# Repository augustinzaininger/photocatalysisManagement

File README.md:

# photocatalysisManagement
PCB Layouts, firmware and software for management of photocatalysis experimental system consisting of MFCs, Solenoid Valves etc

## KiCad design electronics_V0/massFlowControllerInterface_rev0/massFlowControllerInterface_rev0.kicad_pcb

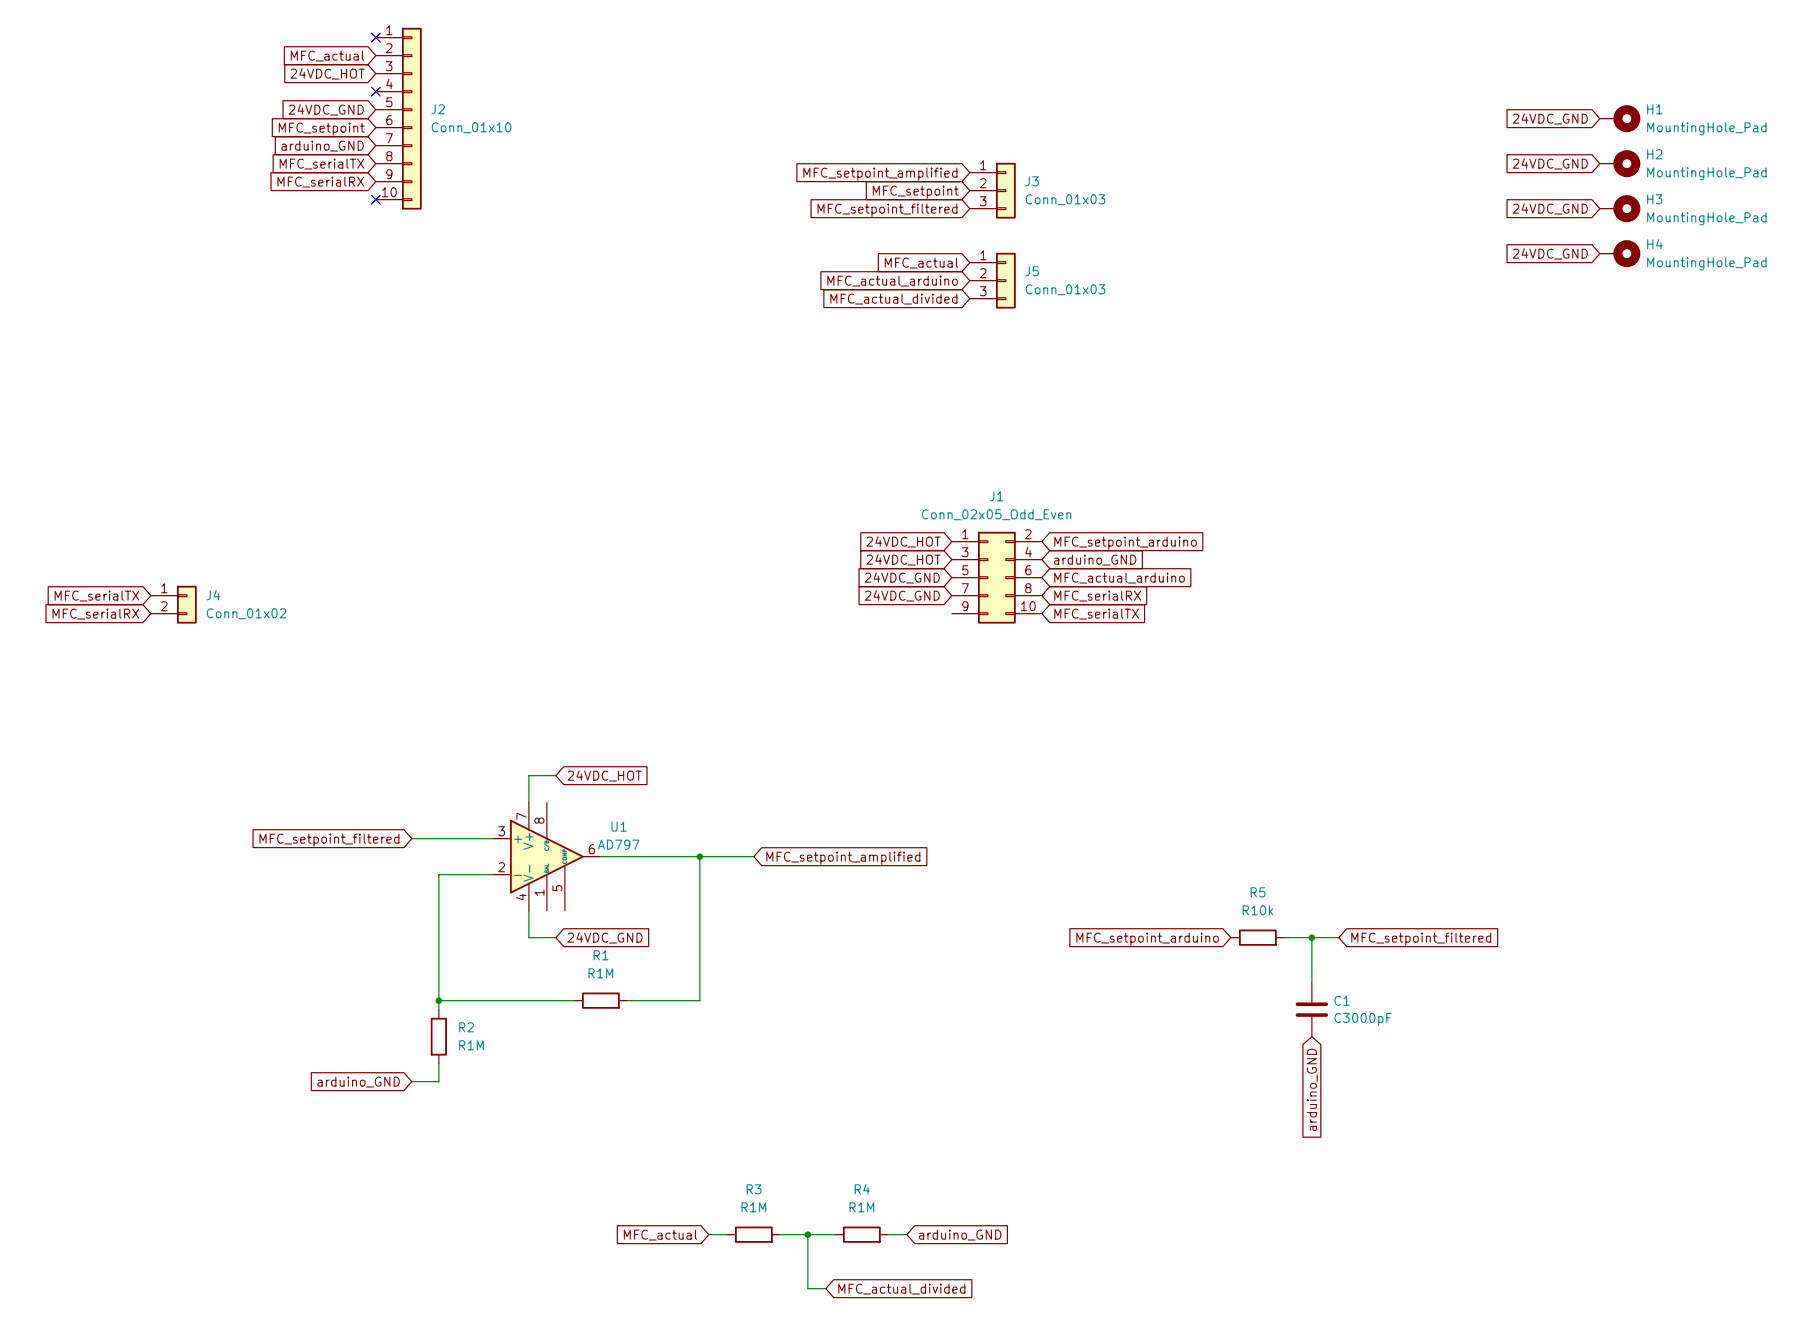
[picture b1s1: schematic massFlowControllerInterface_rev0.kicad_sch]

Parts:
C1: C3000pF; C_0805_2012Metric_Pad1.18x1.45mm_HandSolder
H1, H2, H3, H4: MountingHole_Pad; MountingHole_3.2mm_M3_Pad_Via
J1: Conn_02x05_Odd_Even; PinHeader_2x05_P2.54mm_Vertical
J2: Conn_01x10; multicomp_screwTerminal_10Way_MP008518
J3, J5: Conn_01x03; PinHeader_1x03_P2.54mm_Vertical
J4: Conn_01x02; multicomp_screwTerminal_2Way_MP008513
R1, R2, R3, R4: R1M; R_2010_5025Metric_Pad1.40x2.65mm_HandSolder
R5: R10k; R_2010_5025Metric_Pad1.40x2.65mm_HandSolder
U1: AD797; DIP-8_W7.62mm

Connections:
24VDC_GND: H1.1, H2.1, H3.1, H4.1, J1.5, J1.7, J2.5, U1.4 (V-)
24VDC_HOT: J1.1, J1.3, J2.3, U1.7 (V+)
MFC_actual: J2.2, J5.1, R3.1
MFC_actual_arduino: J1.6, J5.2
MFC_actual_divided: J5.3, R3.2, R4.1
MFC_serialRX: J1.8, J2.9, J4.2
MFC_serialTX: J1.10, J2.8, J4.1
MFC_setpoint: J2.6, J3.2
MFC_setpoint_amplified: J3.1, R1.2, U1.6
MFC_setpoint_arduino: J1.2, R5.1
MFC_setpoint_filtered: C1.1, J3.3, R5.2, U1.3 (+)
unnamed: R1.1, R2.1, U1.2 (-)
arduino_GND: C1.2, J1.4, J2.7, R2.2, R4.2

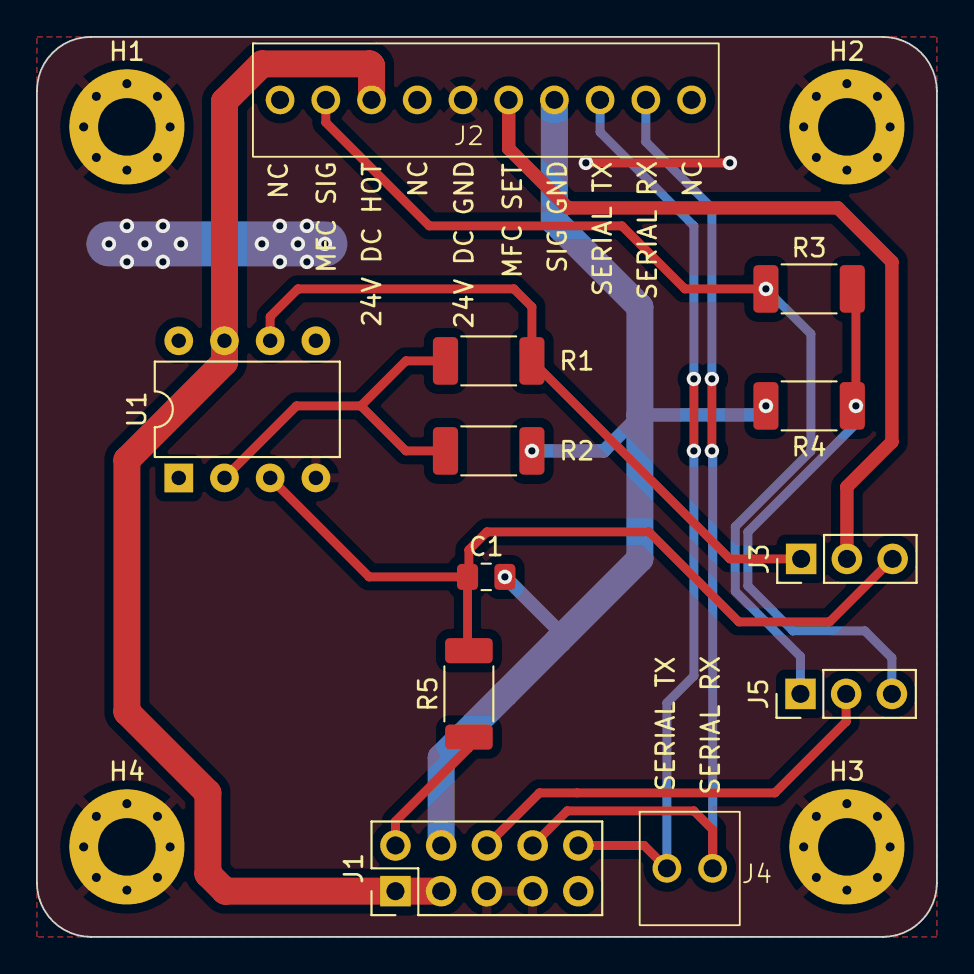
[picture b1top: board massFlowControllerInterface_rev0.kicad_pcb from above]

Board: 2 copper layers, 50.0 x 50.0 mm, 16 parts (0 on the bottom side), 13 nets.

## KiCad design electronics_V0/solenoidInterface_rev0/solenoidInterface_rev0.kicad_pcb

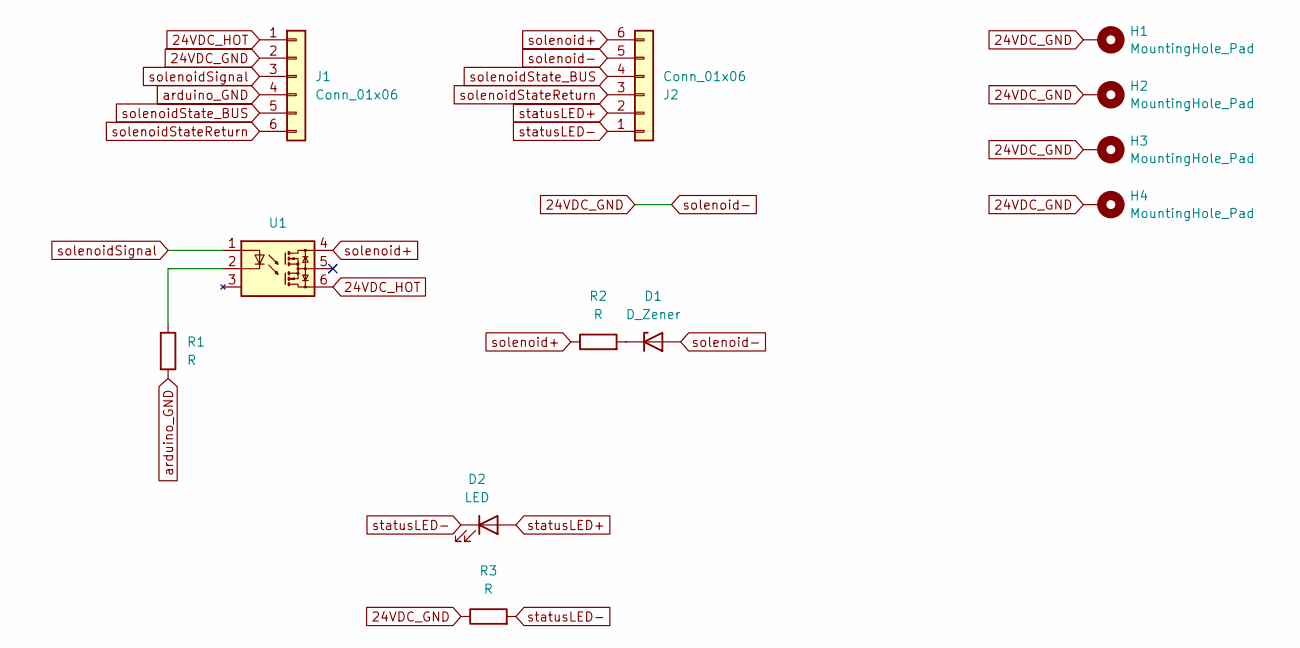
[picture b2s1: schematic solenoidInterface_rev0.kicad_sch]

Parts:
D1: D_Zener; D_A-405_P7.62mm_Horizontal
D2: LED; LED_D3.0mm
H1, H2, H3, H4: MountingHole_Pad; MountingHole_2.5mm_Pad_Via
J1: Conn_01x06; PinHeader_1x06_P2.54mm_Horizontal
J2: Conn_01x06; phoenixContact_MPT_05_254-6way
R1, R2, R3: R; R_2010_5025Metric_Pad1.40x2.65mm_HandSolder
U1: DIP-6_W7.62mm

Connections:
24VDC_GND: D1.2 (A), H1.1, H2.1, H3.1, H4.1, J1.2, J2.5, R3.1
24VDC_HOT: J1.1, U1.6
unnamed: D1.1 (K), R2.2
unnamed: R1.1, U1.2
arduino_GND: J1.4, R1.2
solenoid+: J2.6, R2.1, U1.4
solenoidSignal: J1.3, U1.1
solenoidStateReturn: J1.6, J2.3
solenoidState_BUS: J1.5, J2.4
statusLED+: D2.2 (A), J2.2
statusLED-: D2.1 (K), J2.1, R3.2

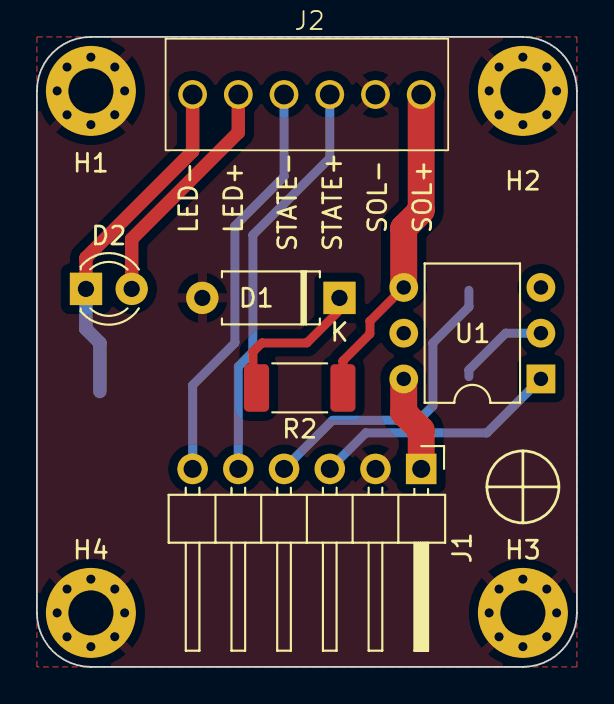
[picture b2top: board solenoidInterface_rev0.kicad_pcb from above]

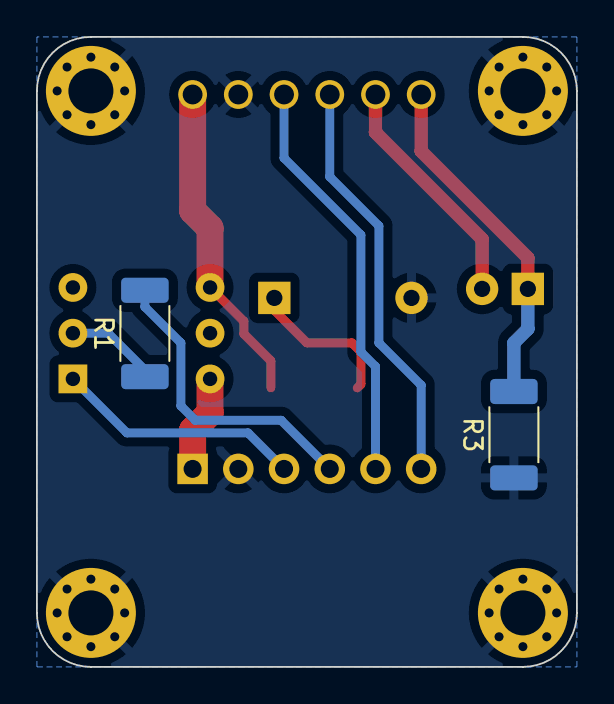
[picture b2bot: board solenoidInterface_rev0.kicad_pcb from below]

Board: 2 copper layers, 30.0 x 35.0 mm, 12 parts (2 on the bottom side), 11 nets.

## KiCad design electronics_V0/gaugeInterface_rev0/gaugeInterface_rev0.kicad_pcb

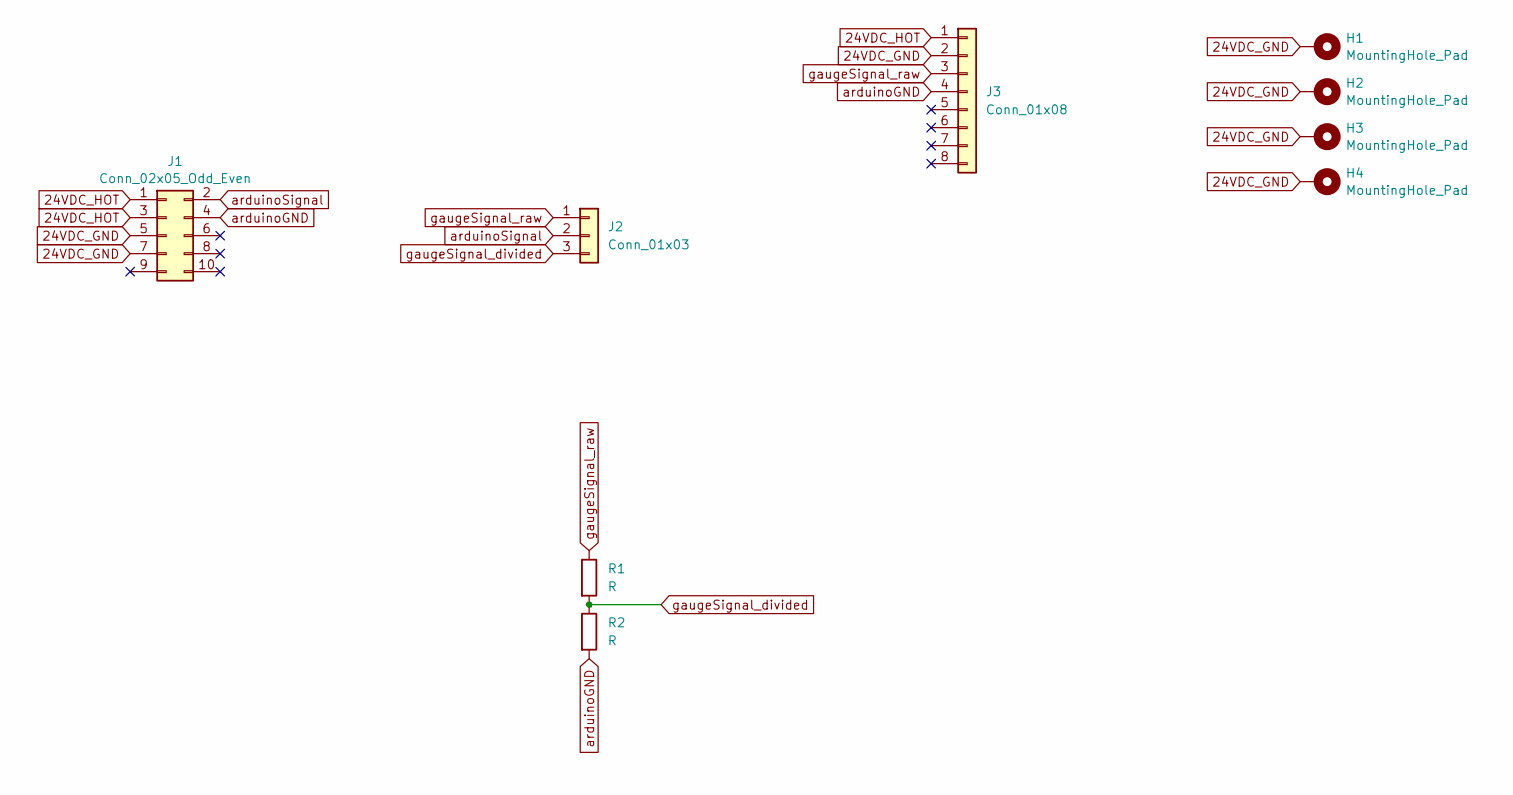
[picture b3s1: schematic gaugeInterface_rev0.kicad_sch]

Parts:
H1, H2, H3, H4: MountingHole_Pad; MountingHole_3.2mm_M3_Pad_Via
J1: Conn_02x05_Odd_Even; PinHeader_2x05_P2.54mm_Vertical
J2: Conn_01x03; PinHeader_1x03_P2.54mm_Vertical
J3: Conn_01x08; phoenixContact_MPT_05_254-8way
R1, R2: R; R_2010_5025Metric_Pad1.40x2.65mm_HandSolder

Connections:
24VDC_GND: H1.1, H2.1, H3.1, H4.1, J1.5, J1.7, J3.2
24VDC_HOT: J1.1, J1.3, J3.1
arduinoGND: J1.4, J3.4, R2.2
arduinoSignal: J1.2, J2.2
gaugeSignal_divided: J2.3, R1.2, R2.1
gaugeSignal_raw: J2.1, J3.3, R1.1

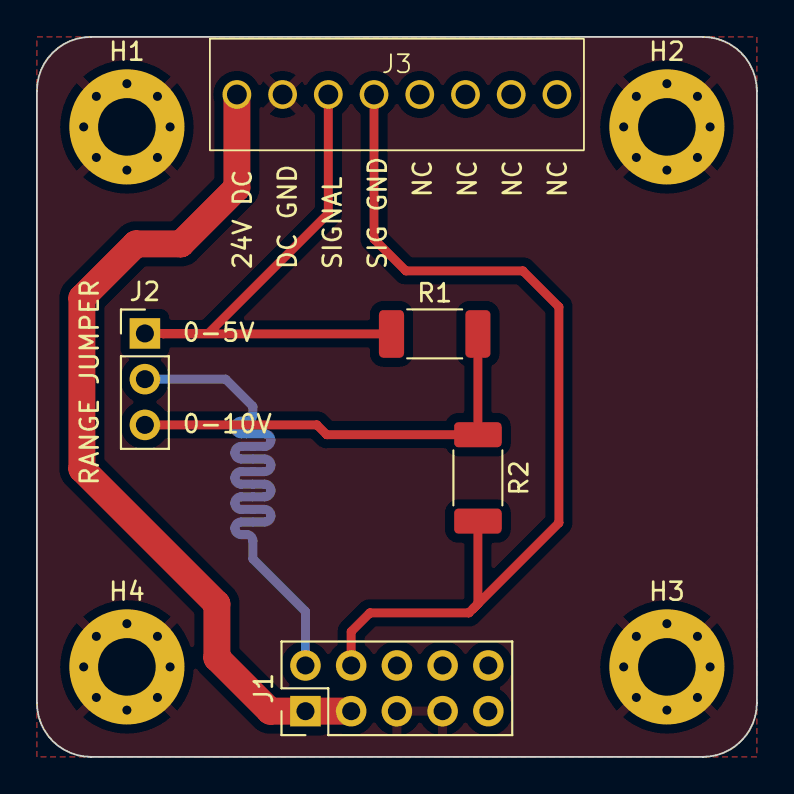
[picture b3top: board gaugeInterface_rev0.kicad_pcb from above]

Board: 2 copper layers, 40.0 x 40.0 mm, 9 parts (0 on the bottom side), 6 nets.

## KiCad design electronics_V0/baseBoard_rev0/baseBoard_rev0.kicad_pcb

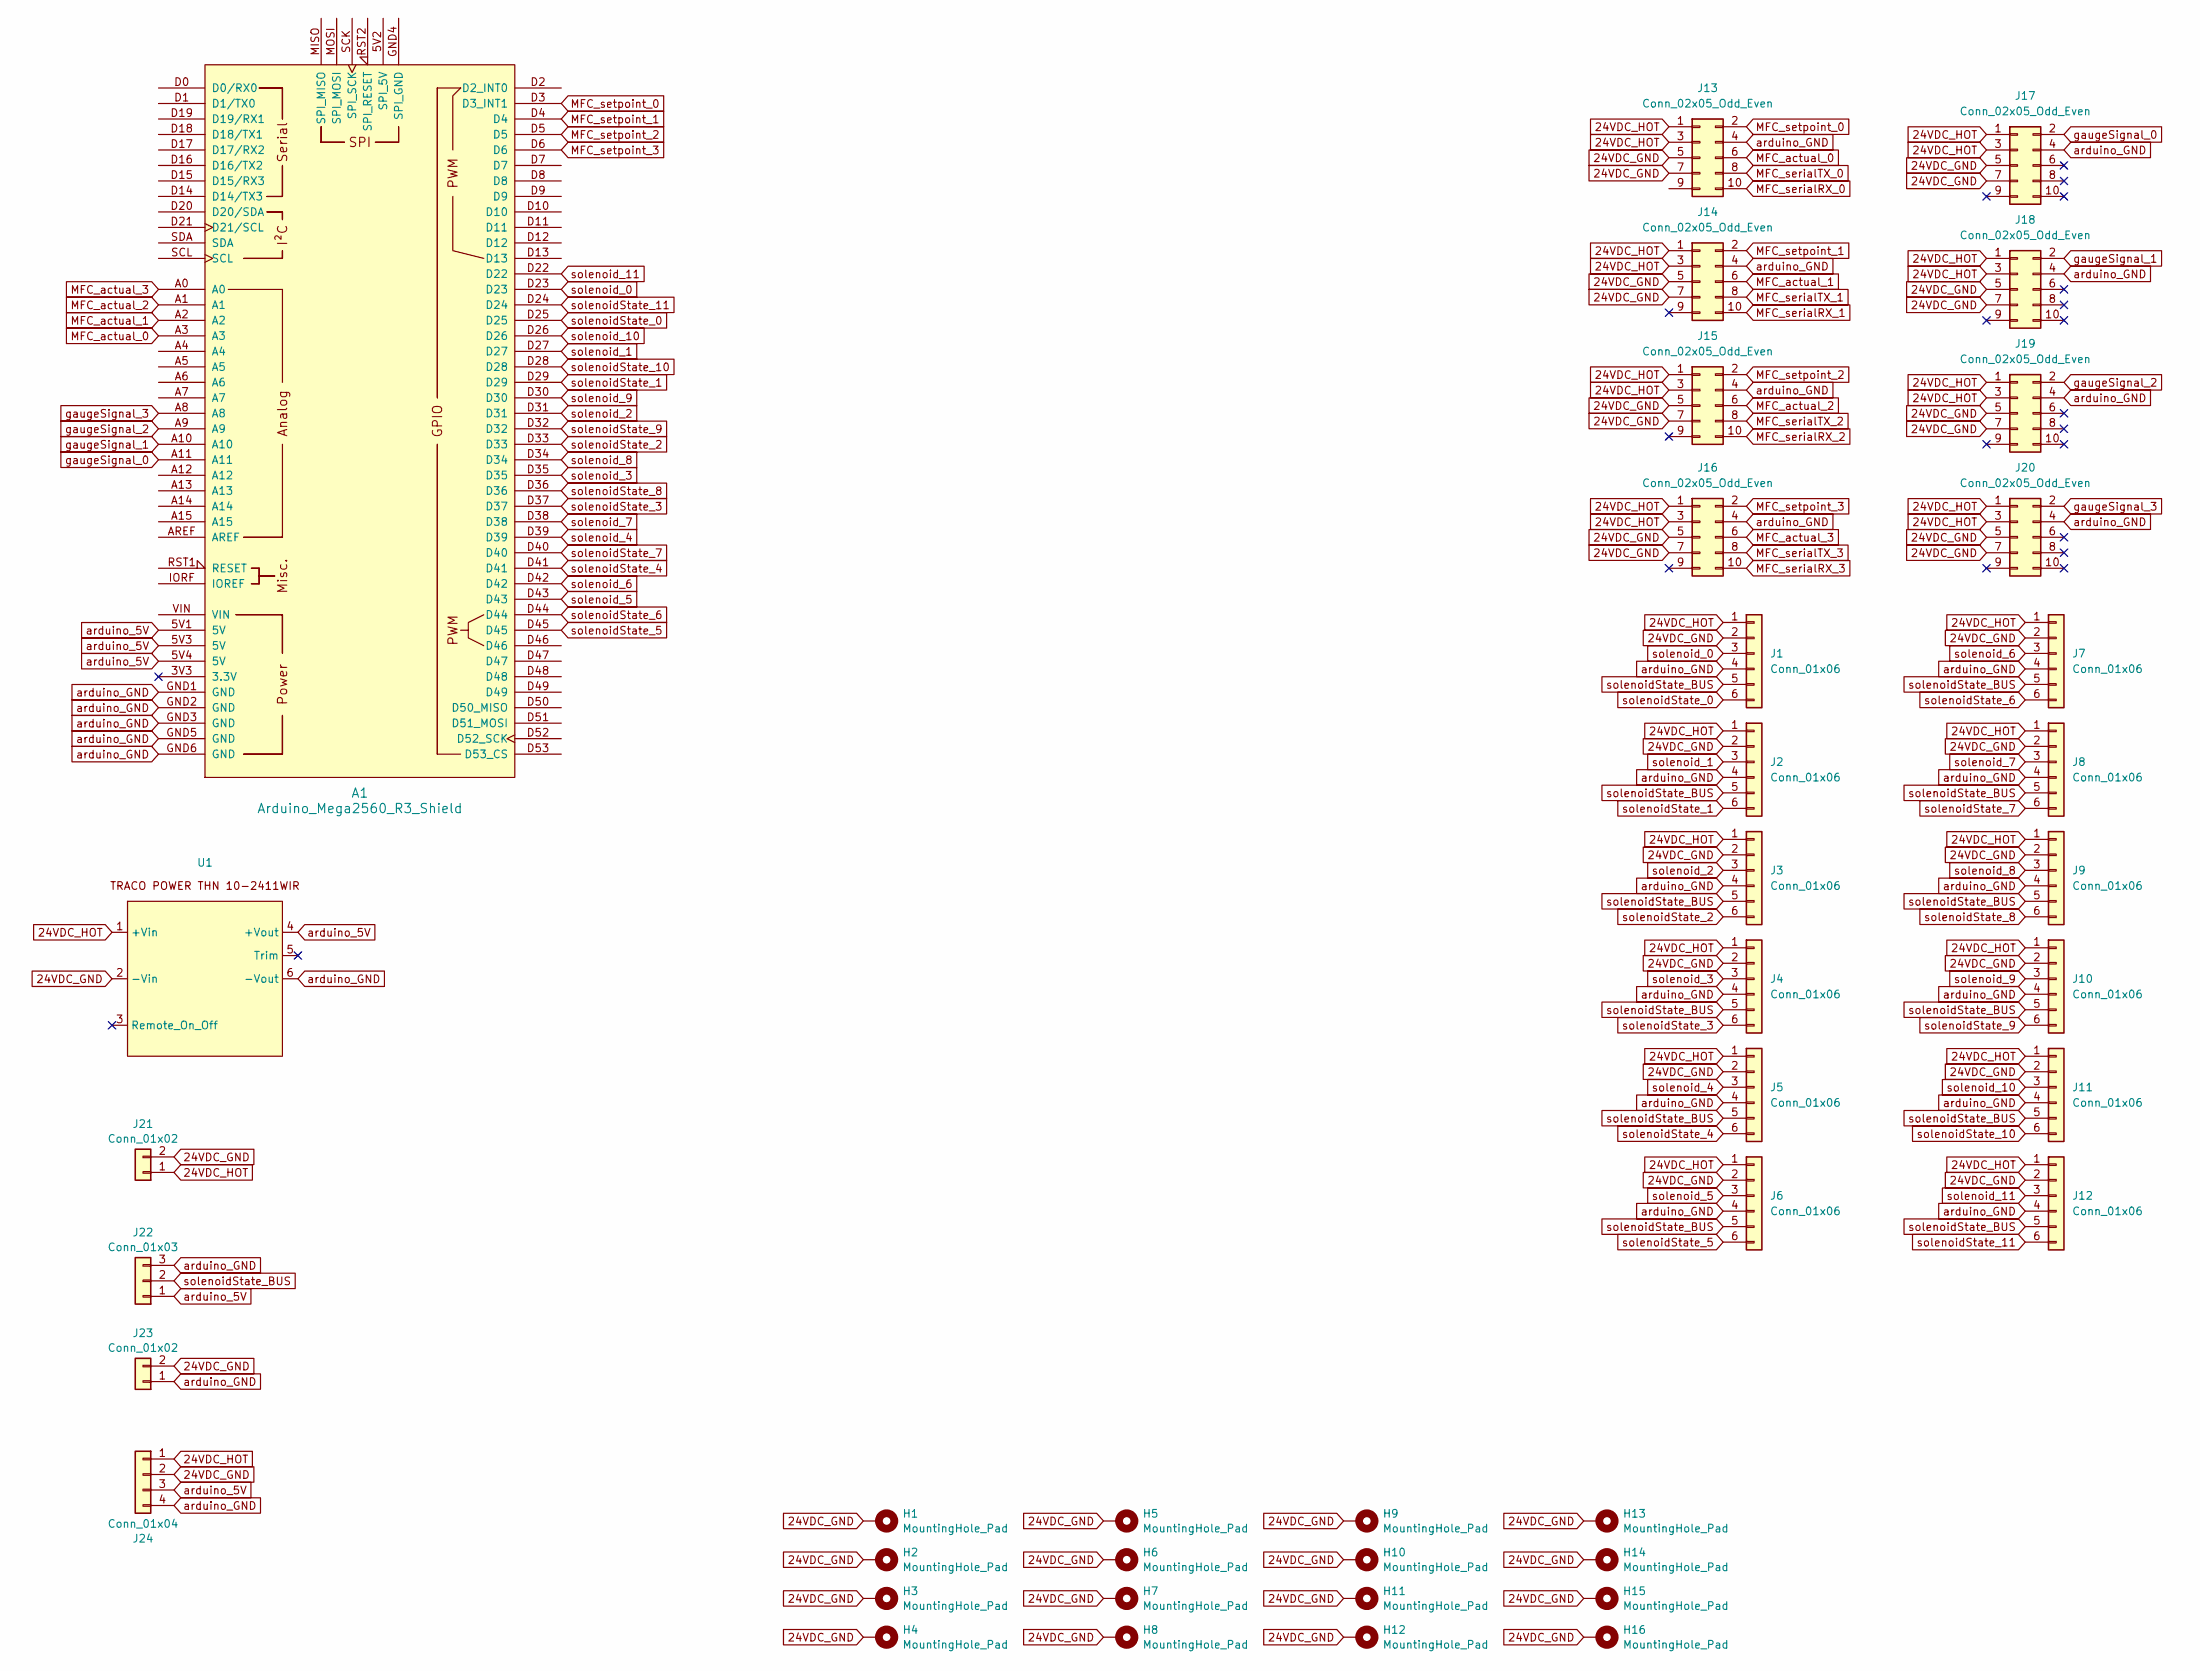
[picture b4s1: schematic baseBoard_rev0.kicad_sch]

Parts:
A1: Arduino_Mega2560_R3_Shield
H1, H2, H3, H4, H5, H6, H7, H8, H9, H10, H11, H12, H13, H14, H15, H16: MountingHole_Pad; MountingHole_3.2mm_M3_Pad_Via
J1, J2, J3, J4, J5, J6, J7, J8, J9, J10, J11, J12: Conn_01x06; PinSocket_1x06_P2.54mm_Vertical
J13, J14, J15, J16, J17, J18, J19, J20: Conn_02x05_Odd_Even; PinHeader_2x05_P2.54mm_Vertical
J21: Conn_01x02; TerminalBlock_Phoenix_MKDS-1,5-2-5.08_1x02_P5.08mm_Horizont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
J22: Conn_01x03; PinHeader_1x03_P2.54mm_Vertical
J23: Conn_01x02; PinHeader_1x02_P2.54mm_Vertical
J24: Conn_01x04; PinHeader_1x04_P2.54mm_Vertical
U1: THN102410WIR

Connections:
24VDC_GND: H1.1, H2.1, H3.1, H4.1, H5.1, H6.1, H7.1, H8.1, H9.1, H10.1, H11.1, H12.1, H13.1, H14.1, H15.1, H16.1, J1.2, J2.2, J3.2, J4.2, J5.2, J6.2, J7.2, J8.2, J9.2, J10.2, J11.2, J12.2, J13.5, J13.7, J14.5, J14.7, J15.5, J15.7, J16.5, J16.7, J17.5, J17.7, J18.5, J18.7, J19.5, J19.7, J20.5, J20.7, J21.2, J23.2, J24.2, U1.2 (-Vin)
24VDC_HOT: J1.1, J2.1, J3.1, J4.1, J5.1, J6.1, J7.1, J8.1, J9.1, J10.1, J11.1, J12.1, J13.1, J13.3, J14.1, J14.3, J15.1, J15.3, J16.1, J16.3, J17.1, J17.3, J18.1, J18.3, J19.1, J19.3, J20.1, J20.3, J21.1, J24.1, U1.1 (+Vin)
MFC_actual_0: A1.A3, J13.6
MFC_actual_1: A1.A2, J14.6
MFC_actual_2: A1.A1, J15.6
MFC_actual_3: A1.A0, J16.6
MFC_serialRX_0: J13.10
MFC_serialRX_1: J14.10
MFC_serialRX_2: J15.10
MFC_serialRX_3: J16.10
MFC_serialTX_0: J13.8
MFC_serialTX_1: J14.8
MFC_serialTX_2: J15.8
MFC_serialTX_3: J16.8
MFC_setpoint_0: A1.D3 (D3_INT1), J13.2
MFC_setpoint_1: A1.D4, J14.2
MFC_setpoint_2: A1.D5, J15.2
MFC_setpoint_3: A1.D6, J16.2
arduino_5V: A1.5V1 (5V), A1.5V3 (5V), A1.5V4 (5V), J22.1, J24.3, U1.4 (+Vout)
arduino_GND: A1.GND1 (GND), A1.GND2 (GND), A1.GND3 (GND), A1.GND5 (GND), A1.GND6 (GND), J1.4, J2.4, J3.4, J4.4, J5.4, J6.4, J7.4, J8.4, J9.4, J10.4, J11.4, J12.4, J13.4, J14.4, J15.4, J16.4, J17.4, J18.4, J19.4, J20.4, J22.3, J23.1, J24.4, U1.6 (-Vout)
gaugeSignal_0: A1.A11, J17.2
gaugeSignal_1: A1.A10, J18.2
gaugeSignal_2: A1.A9, J19.2
gaugeSignal_3: A1.A8, J20.2
solenoidState_0: A1.D25, J1.6
solenoidState_1: A1.D29, J2.6
solenoidState_2: A1.D33, J3.6
solenoidState_3: A1.D37, J4.6
solenoidState_4: A1.D41, J5.6
solenoidState_5: A1.D45, J6.6
solenoidState_6: A1.D44, J7.6
solenoidState_7: A1.D40, J8.6
solenoidState_8: A1.D36, J9.6
solenoidState_9: A1.D32, J10.6
solenoidState_10: A1.D28, J11.6
solenoidState_11: A1.D24, J12.6
solenoidState_BUS: J1.5, J2.5, J3.5, J4.5, J5.5, J6.5, J7.5, J8.5, J9.5, J10.5, J11.5, J12.5, J22.2
solenoid_0: A1.D23, J1.3
solenoid_1: A1.D27, J2.3
solenoid_2: A1.D31, J3.3
solenoid_3: A1.D35, J4.3
solenoid_4: A1.D39, J5.3
solenoid_5: A1.D43, J6.3
solenoid_6: A1.D42, J7.3
solenoid_7: A1.D38, J8.3
solenoid_8: A1.D34, J9.3
solenoid_9: A1.D30, J10.3
solenoid_10: A1.D26, J11.3
solenoid_11: A1.D22, J12.3

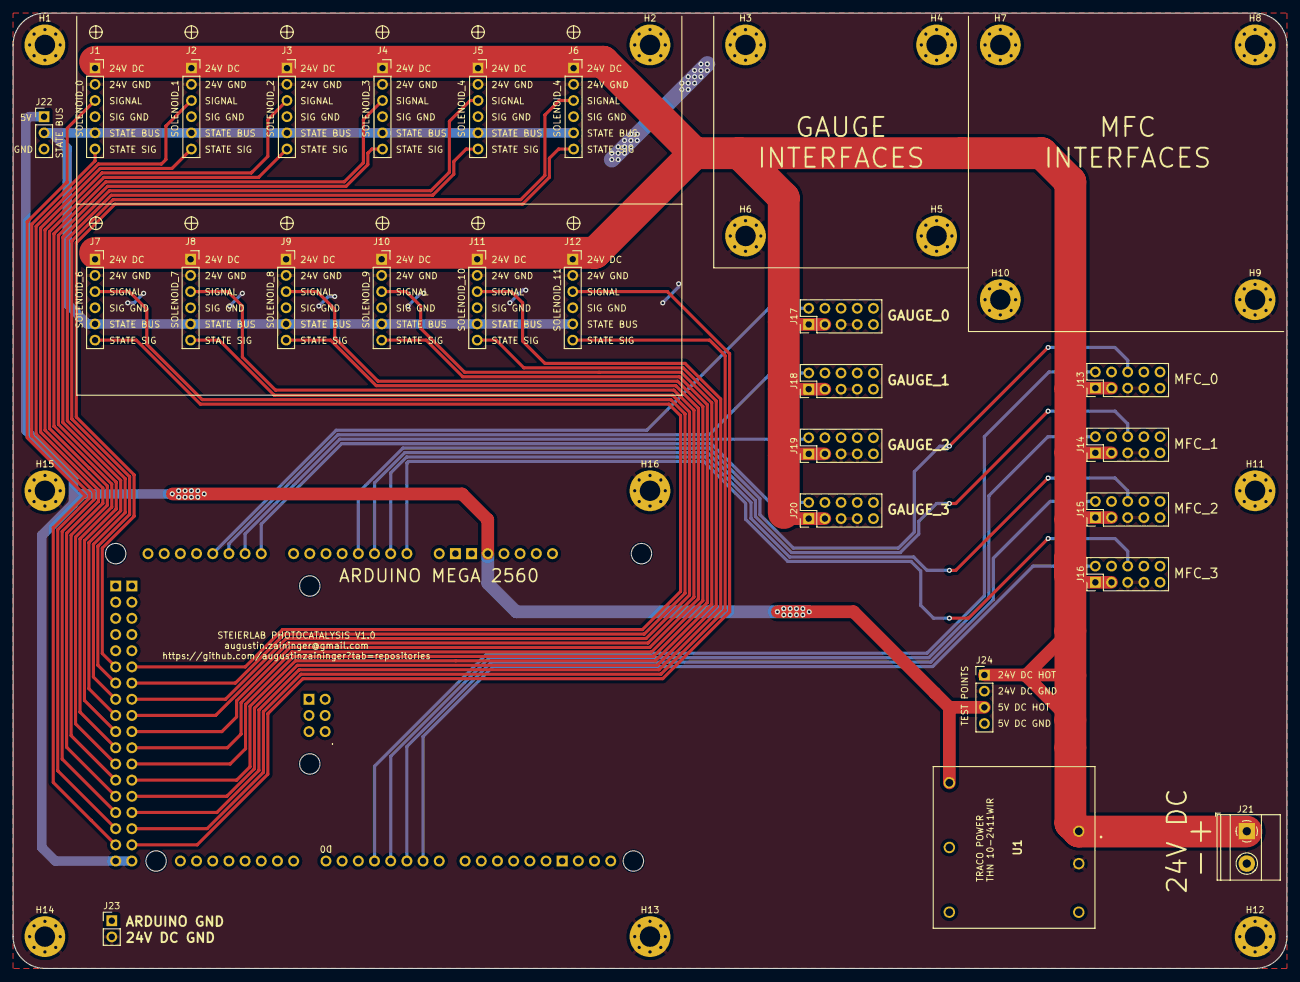
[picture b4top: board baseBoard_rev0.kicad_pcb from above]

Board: 2 copper layers, 200.0 x 150.0 mm, 42 parts (0 on the bottom side), 41 nets.

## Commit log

2024-06-11 Added PCB files
2024-06-11 Added python files
